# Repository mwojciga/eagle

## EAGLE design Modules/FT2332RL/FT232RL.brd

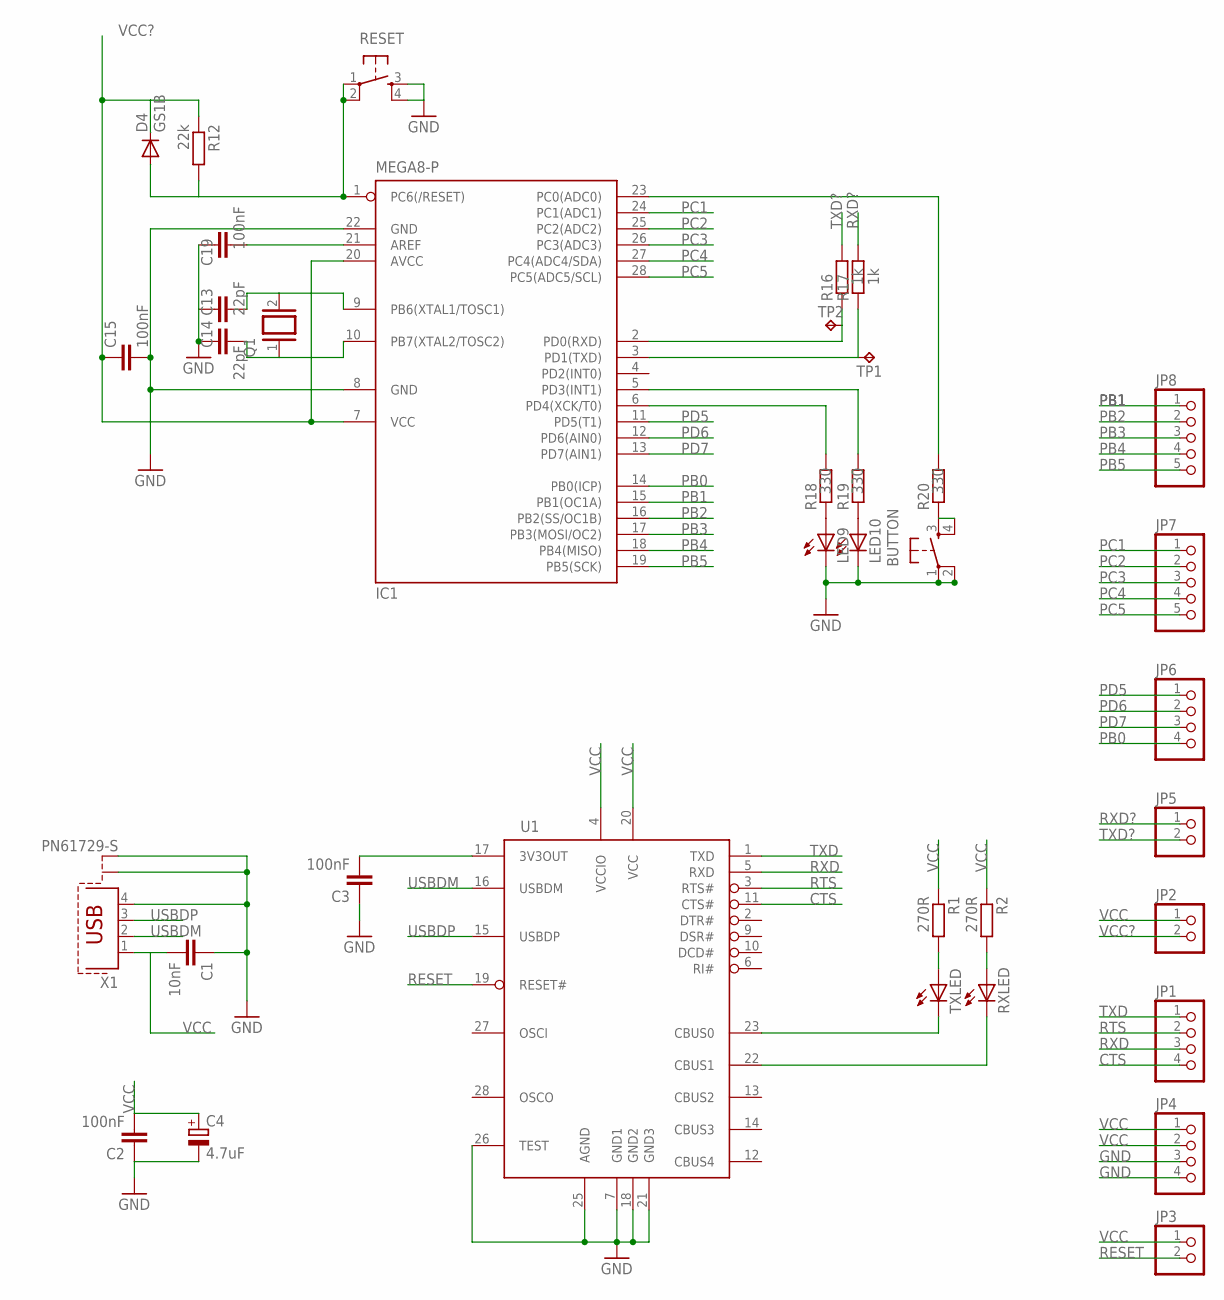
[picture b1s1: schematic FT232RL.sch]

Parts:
BUTTON: TAC_SWITCHSMD; TACTILE_SWITCH_SMD
C1: 10nF; C0805
C2, C3, C15, C19: 100nF; C0805
C4: 4.7uF; E1,8-4
C13, C14: 22pF; C0805
D4: GS1B; DO214AC
IC1: MEGA8-P; DIL28-3
JP1, JP4, JP6: PINHD-1X4; 1X04
JP2, JP3, JP5: PINHD-1X2; 1X02
JP7, JP8: PINHD-1X5; 1X05
LED9, LED10: LEDSMT1206; 1206
Q1: XTAL; Q
R1, R2: 270R; R0805
R12: 22k; R0805
R16, R17: 1k; R0805
R18, R19, R20: 330; R0805
RESET: TAC_SWITCHSMD; TACTILE_SWITCH_SMD
RXLED: LEDSML1206; SML1206
TP1, TP2: TPTP13R; TP13R
TXLED: LEDSML1206; SML1206
U1: FT232RL; SSOP28DB
X1: PN61729-S

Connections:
CTS: JP1.4, U1.11 (CTS#)
GND: BUTTON.1, BUTTON.2, C1.1, C2.1, C3.1, C4.-, C13.1, C14.1, C15.2, C19.2, IC1.8 (GND), IC1.22 (GND), JP4.3, JP4.4, LED9.C, LED10.C, RESET.3, RESET.4, U1.7 (GND1), U1.18 (GND2), U1.21 (GND3), U1.25 (AGND), U1.26 (TEST), X1.4, X1.S1, X1.S2
unnamed: TXLED.C, U1.23 (CBUS0)
unnamed: RXLED.C, U1.22 (CBUS1)
unnamed: R1.2, TXLED.A
unnamed: R2.2, RXLED.A
unnamed: C3.2, U1.17 (3V3OUT)
unnamed: IC1.2 (PD0(RXD)), R16.1, TP2.TP
unnamed: IC1.3 (PD1(TXD)), R17.1, TP1.TP
unnamed: C19.1, IC1.21 (AREF)
unnamed: C14.2, IC1.10 (PB7(XTAL2/TOSC2)), Q1.1
unnamed: C13.2, IC1.9 (PB6(XTAL1/TOSC1)), Q1.2
unnamed: D4.A, IC1.1 (PC6(/RESET)), R12.2, RESET.1, RESET.2
unnamed: BUTTON.3, BUTTON.4, R20.1
unnamed: IC1.6 (PD4(XCK/T0)), R18.2
unnamed: IC1.5 (PD3(INT1)), R19.2
unnamed: IC1.23 (PC0(ADC0)), R20.2
unnamed: LED9.A, R18.1
unnamed: LED10.A, R19.1
PB0: IC1.14 (PB0(ICP)), JP6.4
PB1: IC1.15 (PB1(OC1A)), JP8.1
PB2: IC1.16 (PB2(SS/OC1B)), JP8.2
PB3: IC1.17 (PB3(MOSI/OC2)), JP8.3
PB4: IC1.18 (PB4(MISO)), JP8.4
PB5: IC1.19 (PB5(SCK)), JP8.5
PC1: IC1.24 (PC1(ADC1)), JP7.1
PC2: IC1.25 (PC2(ADC2)), JP7.2
PC3: IC1.26 (PC3(ADC3)), JP7.3
PC4: IC1.27 (PC4(ADC4/SDA)), JP7.4
PC5: IC1.28 (PC5(ADC5/SCL)), JP7.5
PD5: IC1.11 (PD5(T1)), JP6.1
PD6: IC1.12 (PD6(AIN0)), JP6.2
PD7: IC1.13 (PD7(AIN1)), JP6.3
RESET: JP3.2, U1.19 (RESET#)
RTS: JP1.2, U1.3 (RTS#)
RXD: JP1.3, U1.5 (RXD)
RXD?: JP5.1, R17.2
TXD: JP1.1, U1.1 (TXD)
TXD?: JP5.2, R16.2
USBDM: U1.16 (USBDM), X1.2
USBDP: U1.15 (USBDP), X1.3
VCC: C1.2, C2.2, C4.+, JP2.1, JP3.1, JP4.1, JP4.2, R1.1, R2.1, U1.4 (VCCIO), U1.20 (VCC), X1.1
VCC?: C15.1, D4.C, IC1.7 (VCC), IC1.20 (AVCC), JP2.2, R12.1

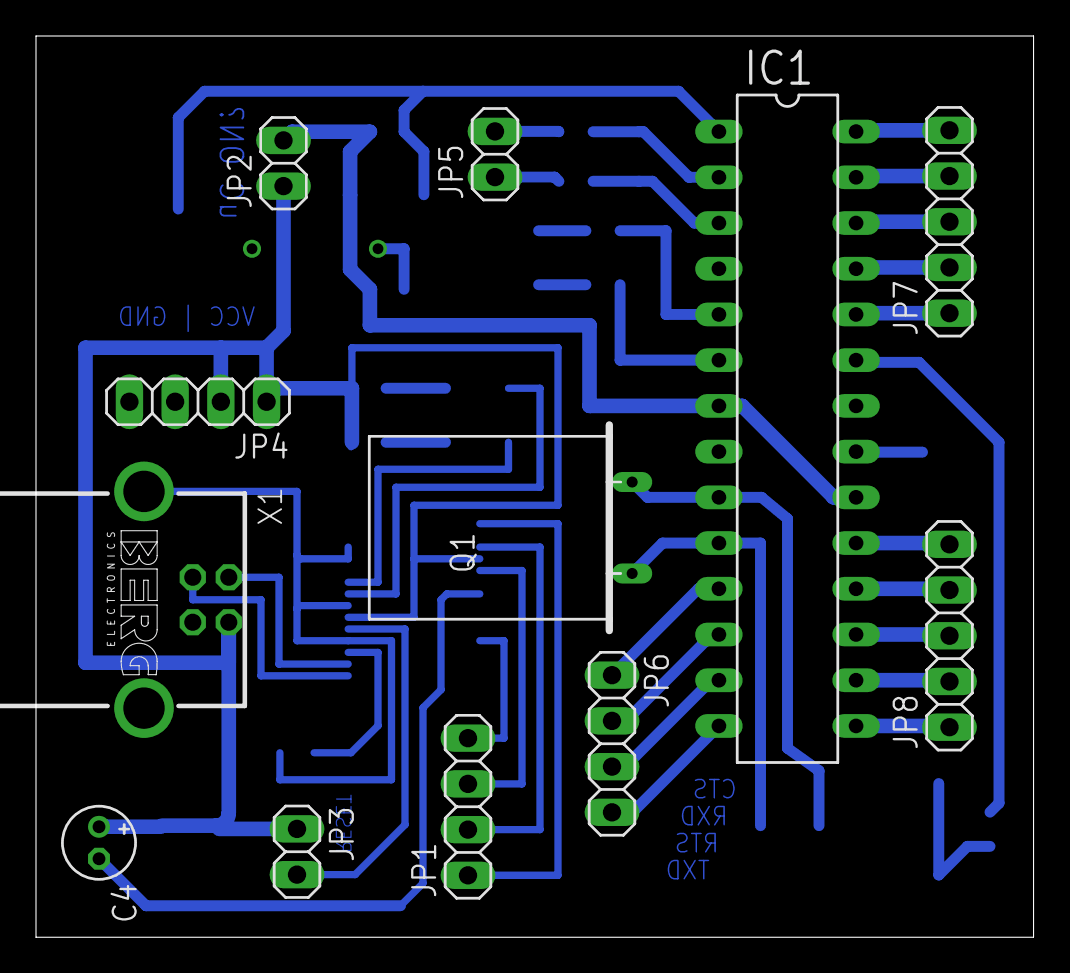
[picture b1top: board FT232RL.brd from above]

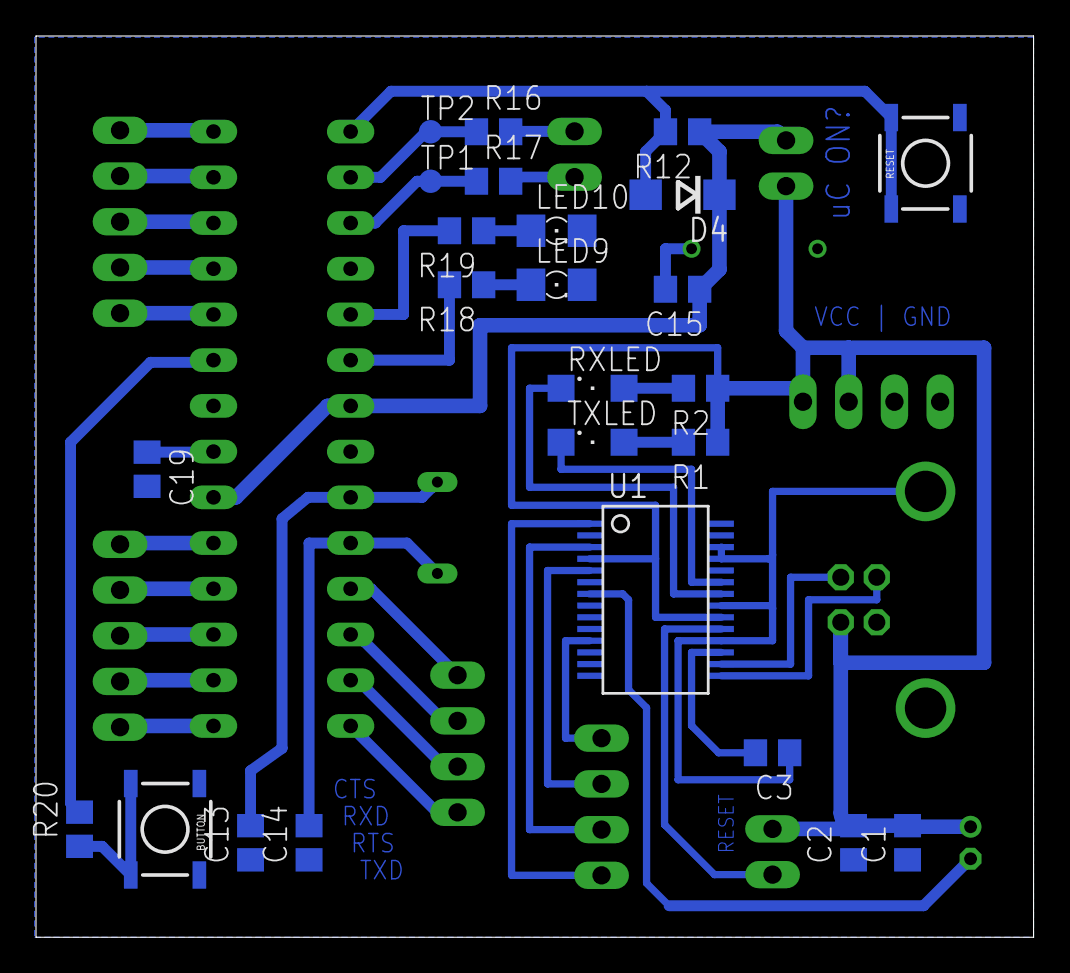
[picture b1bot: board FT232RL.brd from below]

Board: 2 copper layers, 55.4 x 50.1 mm, 37 parts (25 on the bottom side), 43 nets.

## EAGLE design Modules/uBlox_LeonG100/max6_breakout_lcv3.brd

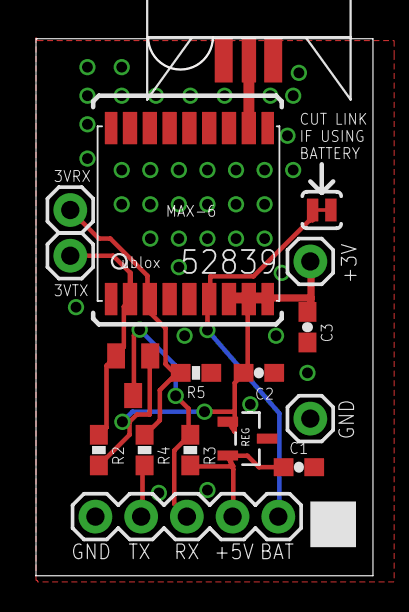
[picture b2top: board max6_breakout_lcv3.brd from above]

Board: 2 copper layers, 18.7 x 29.8 mm, 17 parts (0 on the bottom side), 9 nets.

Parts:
C1, C2, C3: 100nF; 0603-CAP
JP1: 1X05
JP2, JP3, JP4, JP5: M01PTH; 1X01
R2, R3, R4, R5: 10K; 0603-RES
SJ1: SOLDERJUMPERTRACE; SJ_2S-TRACE
U1: LM3480IM3-3.3; SOT95P251X112-3N
U$1: UBLOX_MAX-6
U$2: SARANTEL-SR1202
U$3: BSS138

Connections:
GND: C1.2, C2.2, C3.2, JP1.1, JP2.1, R5.1, SJ1.2, U1.3, U$1.1_GND, U$1.10_GND, U$1.12_GND, U$2.GND1, U$2.GND2
unnamed: U$1.11_RF_IN, U$2.FEED
RX3V3: JP4.1, R4.1, R5.2, U$1.3_RXD1
RX5V: JP1.3, R3.1, U$3.D
TX3V3: JP5.1, R2.1, U$1.2_TXD1, U$3.S
TX5V: JP1.2, R4.2
V5V: C1.1, JP1.4, R3.2, U1.2
VCC: C2.1, C3.1, JP3.1, R2.2, U1.1, U$1.7_VCC_IO, U$1.8_VCC, U$1.9_V_RESET, U$3.G
V_BCKP: JP1.5, SJ1.1, U$1.6_V_BCKP

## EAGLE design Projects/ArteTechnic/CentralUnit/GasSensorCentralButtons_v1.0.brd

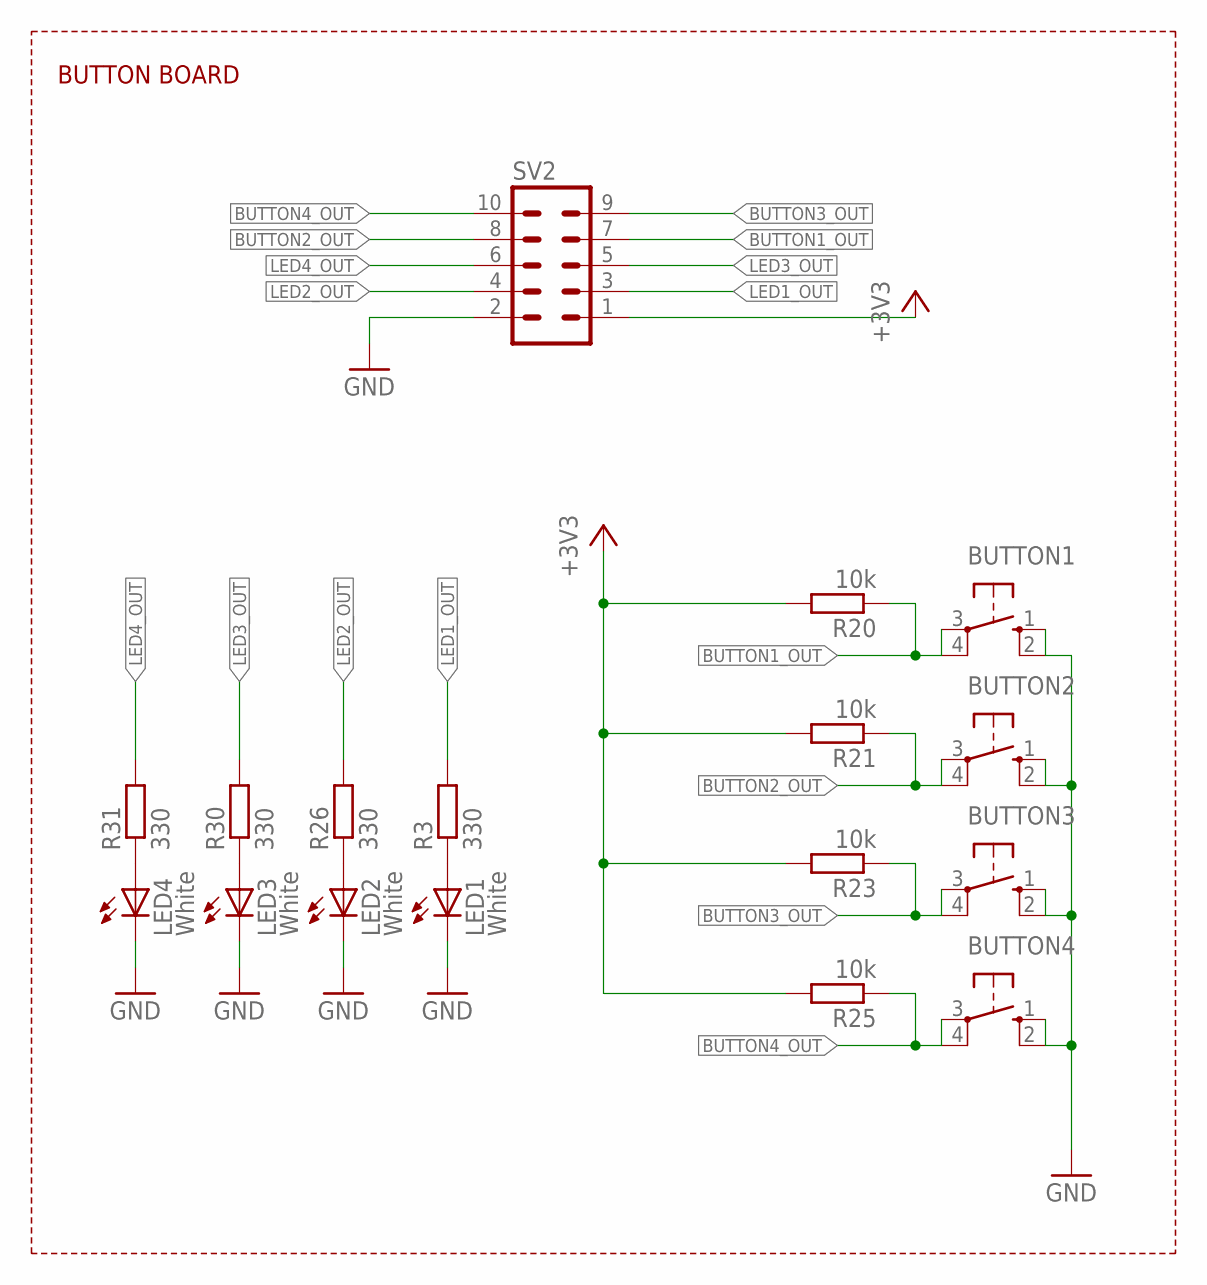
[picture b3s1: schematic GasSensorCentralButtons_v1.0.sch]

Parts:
BUTTON1, BUTTON2, BUTTON3, BUTTON4: 10-XX; B3F-10XX
LED1, LED2, LED3, LED4: White; LED3MM
R3, R26, R30, R31: 330; 0207/10
R20, R21, R23, R25: 10k; 0207/10
SV2: ML10

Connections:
+3V3: R20.2, R21.2, R23.2, R25.2, SV2.1
BUTTON1_OUT: BUTTON1.3, BUTTON1.4 (P1), R20.1, SV2.7
BUTTON2_OUT: BUTTON2.3, BUTTON2.4 (P1), R21.1, SV2.8
BUTTON3_OUT: BUTTON3.3, BUTTON3.4 (P1), R23.1, SV2.9
BUTTON4_OUT: BUTTON4.3, BUTTON4.4 (P1), R25.1, SV2.10
GND: BUTTON1.1 (S), BUTTON1.2 (S1), BUTTON2.1 (S), BUTTON2.2 (S1), BUTTON3.1 (S), BUTTON3.2 (S1), BUTTON4.1 (S), BUTTON4.2 (S1), LED1.K (C), LED2.K (C), LED3.K (C), LED4.K (C), SV2.2
LED1_OUT: R3.2, SV2.3
LED2_OUT: R26.2, SV2.4
LED3_OUT: R30.2, SV2.5
LED4_OUT: R31.2, SV2.6
unnamed: LED1.A, R3.1
unnamed: LED2.A, R26.1
unnamed: LED3.A, R30.1
unnamed: LED4.A, R31.1

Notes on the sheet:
BUTTON BOARD

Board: 2 copper layers, 17 parts (0 on the bottom side), 14 nets, no tracks yet.

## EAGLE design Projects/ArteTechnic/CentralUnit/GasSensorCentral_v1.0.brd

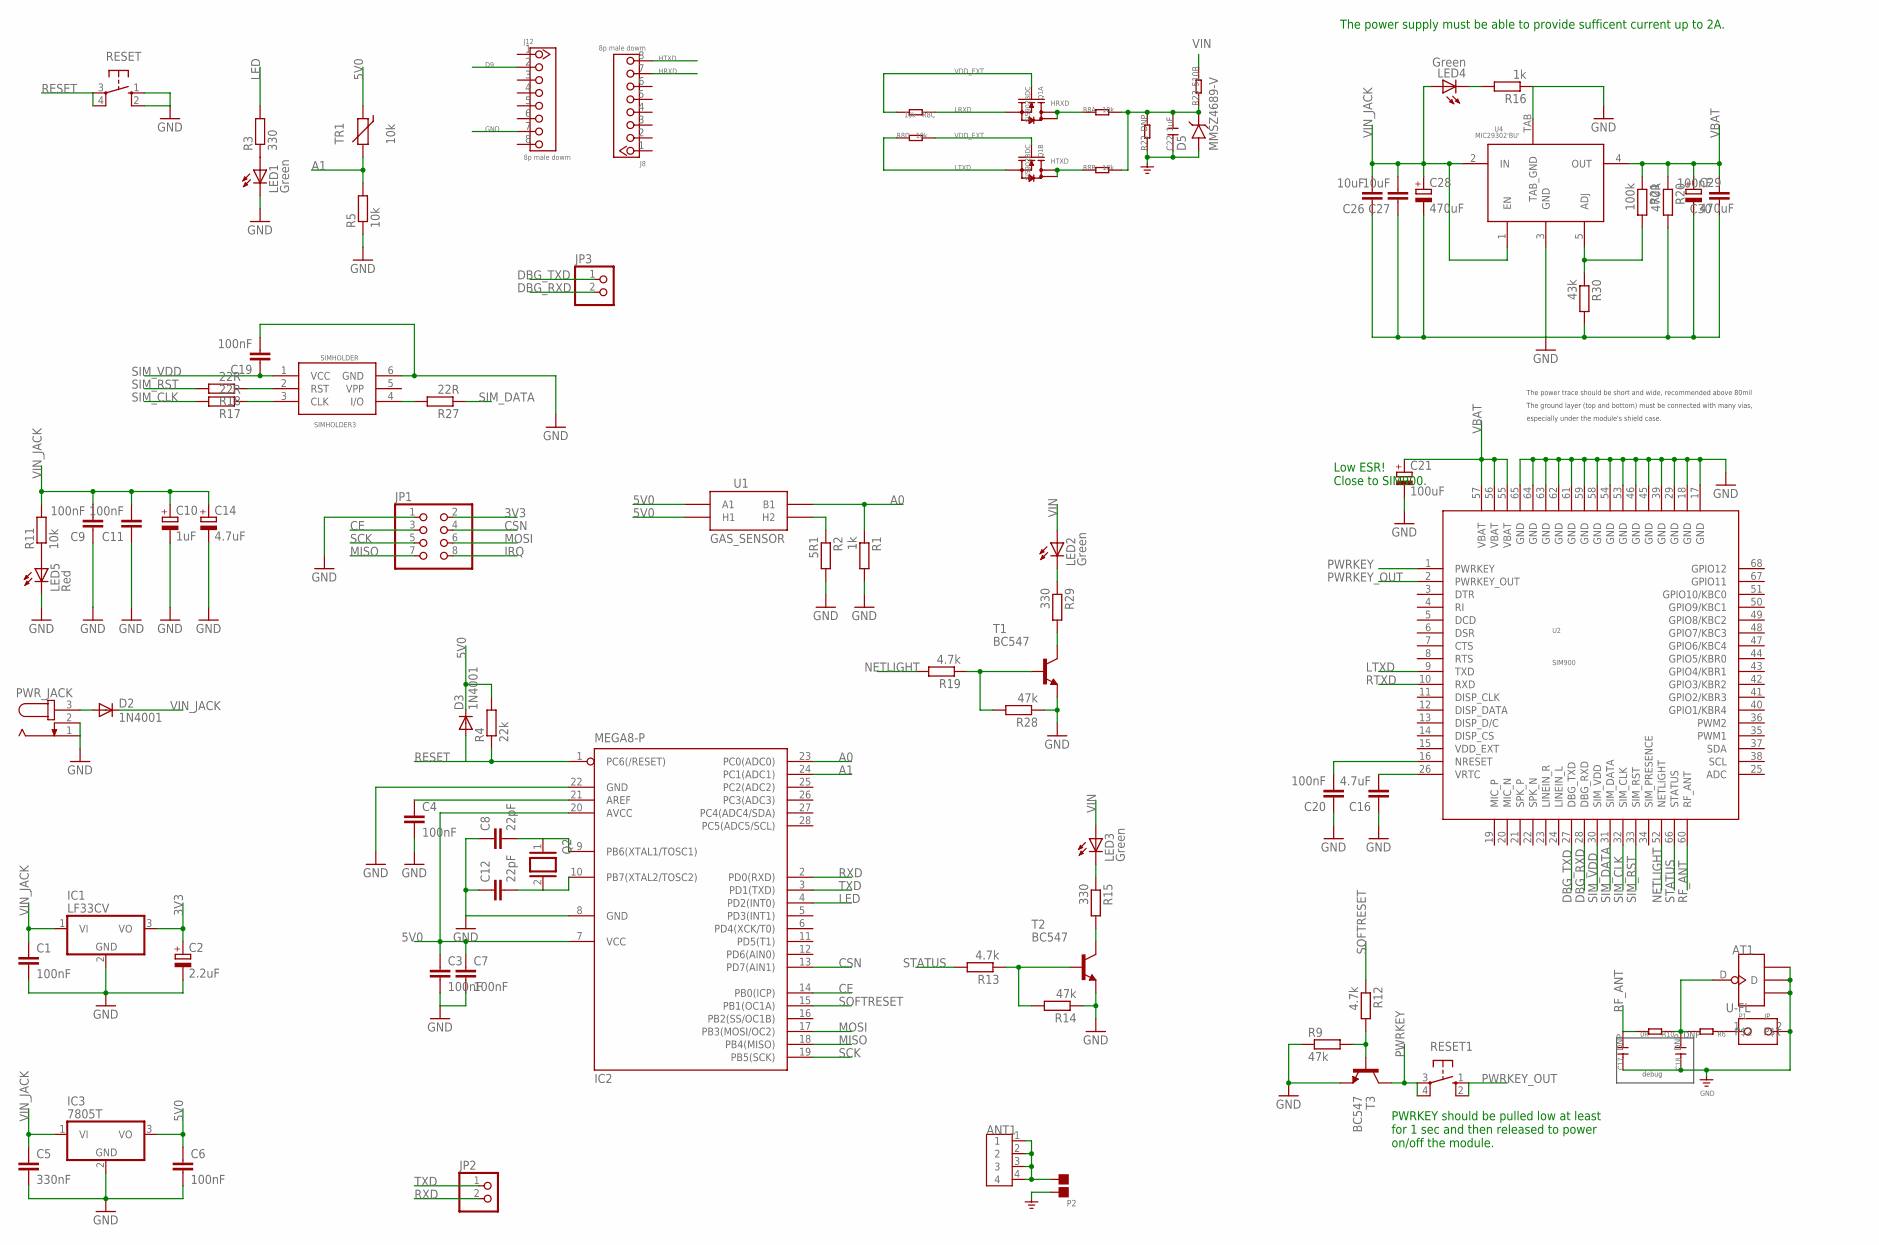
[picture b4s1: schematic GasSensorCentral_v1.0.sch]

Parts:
ANT1: ANTENNA-SMA-IPX; SMA-TO-IPX
AT1: U-FL; 4P-U-FL
C1, C3, C4, C6, C7, C9, C11, C19, C20, C30: 100nF; C025-025X050
C2: 2.2uF; E2,5-5
C5: 330nF; C025-025X050
C8, C12: 22pF; C025-025X050
C10: 1uF; E2,5-5
C14: 4.7uF; E2,5-5
C16: 4.7uF; C025-025X050
C17, C18: DNP; 0402
C21: 100uF; E2,5-5
C22: 1uF; 0603
C26, C27: 10uF; C025-025X050
C28, C29: 470uF; E2,5-5
D2, D3: 1N4001; DO41-10
D5: MMSZ4689-V; SOD123-2.7X1.6
IC1: LF33CV; TO220H
IC2: MEGA8-P; DIL28-3
IC3: 7805T; TO220H
J8, J12: 8p male dowm; CK_1X8
JP1: PINHD-2X4; 2X04
JP2, JP3: PINHD-1X2/90; 1X02/90
LED1, LED2, LED3, LED4: Green; LED3MM
LED5: Red; LED3MM
P1: JP
P2: PAD-JUMPER-2P; 2P-SMD-1.78X1.27
PWR_JACK: JACK-PLUG0; SPC4077
Q1: Si5902BDC; 1206-8
Q2: XTAL/S; QS
R1, R16: 1k; 0207/10
R2: 5R1; 0207/10
R3, R15, R29: 330; 0207/10
R4: 22k; 0207/10
R5, R11: 10k; 0207/10
R6: DNP; 0402
R8: 10k; 1206-8-3.3X2.4
R9, R14, R28: 47k; 0207/10
R10: 0R; 0402
R12, R13, R19: 4.7k; 0207/10
R17, R18, R27: 22R; 0207/10
R20: 470R; 0207/10
R21: 100k; 0207/10
R22: DNP; 0603
R23: 510R; 0603
R30: 43k; 0207/10
RESET, RESET1: 10-XX; B3F-10XX
SIMHOLDER: SIMHOLDER3
T1, T2, T3: BC547; TO92
TR1: 10k; RS-2,5
U1: GAS_SENSOR; MQ-3
U2: SIM900
U4: MIC29302'BU'; TO-263

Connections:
3V3: C2.+, IC1.3 (VO), JP1.2
5V0: C3.1, C6.1, C7.1, D3.C, IC2.7 (VCC), IC2.20 (AVCC), IC3.3 (VO), R4.2, TR1.1, U1.A1, U1.HA (H1)
A0: IC2.23 (PC0(ADC0)), R1.1, U1.B1
A1: IC2.24 (PC1(ADC1)), R5.2, TR1.2
CE: IC2.14 (PB0(ICP)), JP1.3
CSN: IC2.13 (PD7(AIN1)), JP1.4
D9: J12.2
DBG_RXD: JP3.2, U2.28 (DBG_RXD)
DBG_TXD: JP3.1, U2.27 (DBG_TXD)
GND: AT1.GND1, AT1.GND2, AT1.GND3, C1.2, C2.-, C3.2, C4.2, C5.2, C6.2, C7.2, C8.1, C9.1, C10.-, C11.1, C12.1, C14.-, C16.1, C17.1, C18.1, C19.2, C20.1, C21.-, C22.1, C26.1, C27.1, C28.-, C29.-, C30.1, D5.1, IC1.2 (GND), IC2.8 (GND), IC2.22 (GND), IC3.2 (GND), J12.7, JP1.1, LED1.K (C), LED5.K (C), P1.2, P2.2, PWR_JACK.1, PWR_JACK.2, R1.2, R2.2, R5.1, R9.1, R14.1, R16.1, R20.2, R22.1, R28.1, R30.2, RESET.1 (S), RESET.2 (S1), SIMHOLDER.6 (GND), T1.1 (E), T2.1 (E), T3.1 (E), U2.17 (GND), U2.18 (GND), U2.29 (GND), U2.39 (GND), U2.45 (GND), U2.46 (GND), U2.53 (GND), U2.54 (GND), U2.58 (GND), U2.59 (GND), U2.61 (GND), U2.62 (GND), U2.63 (GND), U2.64 (GND), U2.65 (GND), U4.3 (GND), U4.TAB (TAB_GND)
HRXD: J8.7, Q1.7 (D), Q1.8 (D), R8.1
HTXD: J8.8, Q1.5 (D), Q1.6 (D), R8.2 (1)
IRQ: JP1.8
LED: IC2.4 (PD2(INT0)), R3.2
LRXD: Q1.1 (S), R8.3 (1)
LTXD: Q1.3 (S), R8.4 (1), U2.9 (TXD)
MISO: IC2.18 (PB4(MISO)), JP1.7
MOSI: IC2.17 (PB3(MOSI/OC2)), JP1.6
unnamed: C4.1, IC2.21 (AREF)
unnamed: R2.1, U1.HB (H2)
unnamed: D2.A, PWR_JACK.3
unnamed: LED1.A, R3.1
unnamed: R27.2, SIMHOLDER.4 (I/O)
unnamed: LED2.K (C), R29.1
unnamed: R29.2, T1.3 (C)
unnamed: R13.1, R14.2, T2.2 (B)
unnamed: LED5.A, R11.1
unnamed: LED3.K (C), R15.1
unnamed: R15.2, T2.3 (C)
unnamed: C20.2, U2.16 (NRESET)
unnamed: R9.2, R12.2, T3.2 (B)
unnamed: R19.1, R28.2, T1.2 (B)
unnamed: R21.2, R30.1, U4.5 (ADJ)
unnamed: C16.2, U2.26 (VRTC)
unnamed: AT1.D, C18.2, R6.2, R10.1
unnamed: P1.1, R6.1
unnamed: LED4.K (C), R16.2
unnamed: R18.1, SIMHOLDER.2 (RST)
unnamed: R17.1, SIMHOLDER.3 (CLK)
unnamed: C8.2, IC2.9 (PB6(XTAL1/TOSC1)), Q2.1
unnamed: C12.2, IC2.10 (PB7(XTAL2/TOSC2)), Q2.2
unnamed: C22.2, D5.2, R8.7 (2), R8.8 (2), R22.2, R23.1
unnamed: ANT1.1, ANT1.2, ANT1.3, ANT1.4, P2.1
NETLIGHT: R19.2, U2.52 (NETLIGHT)
PWRKEY: RESET1.3, RESET1.4 (P1), T3.3 (C), U2.1 (PWRKEY)
PWRKEY_OUT: RESET1.1 (S), RESET1.2 (S1), U2.2 (PWRKEY_OUT)
RESET: D3.A, IC2.1 (PC6(/RESET)), R4.1, RESET.3, RESET.4 (P1)
RF_ANT: C17.2, R10.2, U2.60 (RF_ANT)
RTXD: U2.10 (RXD)
RXD: IC2.2 (PD0(RXD)), JP2.2
SCK: IC2.19 (PB5(SCK)), JP1.5
SIM_CLK: R17.2, U2.32 (SIM_CLK)
SIM_DATA: R27.1, U2.31 (SIM_DATA)
SIM_RST: R18.2, U2.33 (SIM_RST)
SIM_VDD: C19.1, SIMHOLDER.1 (VCC), U2.30 (SIM_VDD)
SOFTRESET: IC2.15 (PB1(OC1A)), R12.1
STATUS: R13.2, U2.66 (STATUS)
TXD: IC2.3 (PD1(TXD)), JP2.1
VBAT: C21.+, C29.+, C30.2, R20.1, R21.1, U2.55 (VBAT), U2.56 (VBAT), U2.57 (VBAT), U4.4 (OUT)
VDD_EXT: Q1.2 (G), Q1.4 (G), R8.5 (2), R8.6 (2)
VIN: LED2.A, LED3.A, R23.2
VIN_JACK: C1.1, C5.1, C9.2, C10.+, C11.2, C14.+, C26.2, C27.2, C28.+, D2.C, IC1.1 (VI), IC3.1 (VI), LED4.A, R11.2, U4.1 (EN), U4.2 (IN)

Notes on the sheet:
debug
The power trace should be short and wide, recommended above 80mil
The ground layer (top and bottom) must be connected with many vias,
especially under the module's shield case.
PWRKEY should be pulled low at least for 1 sec and then released to power on/off the module.
The power supply must be able to provide sufficent current up to 2A.
Low ESR! Close to SIM900.

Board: 2 copper layers, 84 parts (0 on the bottom side), 59 nets, no tracks yet.

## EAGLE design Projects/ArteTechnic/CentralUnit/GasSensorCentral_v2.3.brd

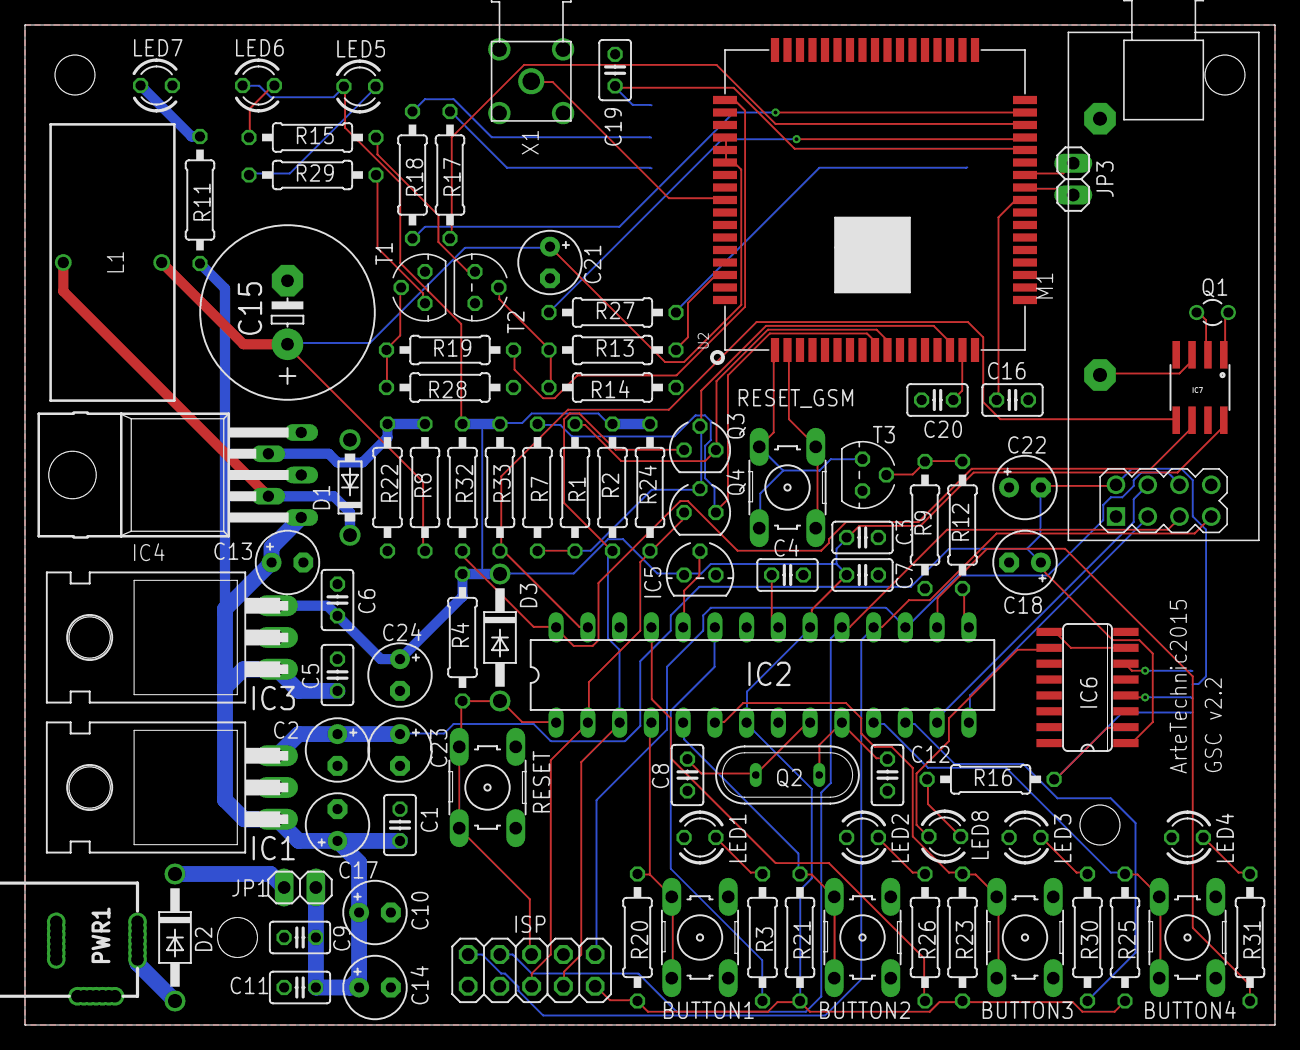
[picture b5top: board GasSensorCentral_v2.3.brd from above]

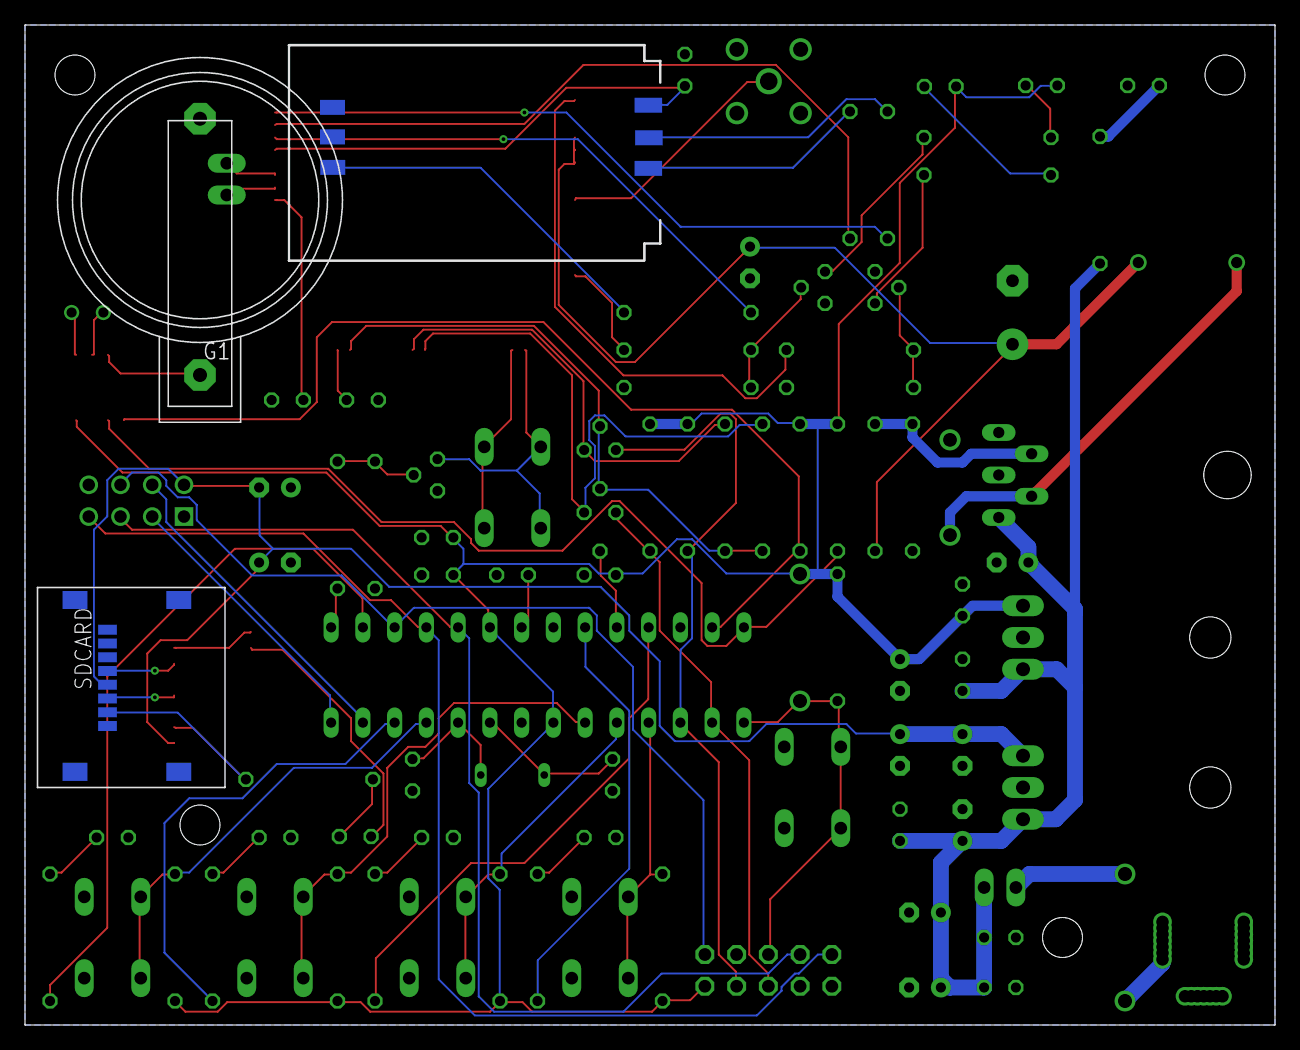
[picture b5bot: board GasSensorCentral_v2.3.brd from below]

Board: 2 copper layers, 100.0 x 80.0 mm, 96 parts (3 on the bottom side), 72 nets.

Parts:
BUTTON1, BUTTON2, BUTTON3, BUTTON4: B3F-10XX
C1, C3, C4, C6, C7, C9, C11, C19, C20: 100nF; C025-025X050
C2: 2.2uF; E2,5-5
C5: 330nF; C025-025X050
C8, C12: 22pF; C025-025X050
C10, C17, C22, C23, C24: 1uF; E2,5-5
C13, C21: 100uF; E2,5-5
C14: 4.7uF; E2,5-5
C15: 3300uF; E5-13
C16: 4.7uF; C025-025X050
C18: 10uF; E2,5-5
D1: 1N5823; DO41-7.6
D2, D3: 1N4001; DO41-10
G1: CR2032H
IC1: LF33CV; TO220H
IC2: MEGA8-P; DIL28-3
IC3: 7805T; TO220H
IC4: LM2576H; TO220-52
IC5: LM35CZ; TO92
IC6: 4050D; SO16
IC7: DS1307SO8; SO08
ISP: 2X05
JP1, JP3: 1X02
L1: 68uH; TJ4-U1
LED1, LED2, LED3, LED4: White; LED3MM
LED5, LED6, LED7: Blue; LED3MM
LED8: Yellow; LED3MM
M1: NRF24L01; WIRELESS-NRD24L01-PA-EXT
PWR1: PWR_JACK_UNI_MILLING
Q1: 32.768K-20PPM; TC26V
Q2: QS
Q3, Q4: BS170; SOT54E
R1, R2, R7, R11, R20, R21, R23, R24, R25, R32, R33: 10k; 0207/10
R3, R15, R26, R29, R30, R31: 330; 0207/10
R4: 22k; 0207/10
R8: 3.6k; 0207/10
R9, R14, R28: 47k; 0207/10
R12, R13, R19: 4.7k; 0207/10
R16: 1k; 0207/10
R17, R18, R27: 22R; 0207/10
R22: 1.5k; 0207/10
RESET: B3F-10XX
RESET_GSM: B3F-10XX
SDCARD: MX-47219-2001
SIMHOLDER: SIMHOLDER3
T1, T2, T3: BC547; TO92
U2: SIM900
X1: BU-SMA-G

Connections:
3V3: C2.+, C18.+, C22.-, C23.+, IC1.3, IC6.1, M1.2, SDCARD.4
5V0: C3.1, C6.1, C7.1, C24.+, D3.C, IC2.7, IC2.20, IC3.3, IC5.1, IC7.8, ISP.2, LED5.A, LED6.A, R2.2, R4.2, R20.2, R21.2, R23.2, R24.2, R25.2, R32.1, R33.1
BUTTON1: BUTTON1.3, BUTTON1.4, IC2.4, R20.1
BUTTON2: BUTTON2.3, BUTTON2.4, IC2.5, R21.1
BUTTON3: BUTTON3.3, BUTTON3.4, IC2.6, R23.1
BUTTON4: BUTTON4.3, BUTTON4.4, IC2.11, R25.1
CE: IC2.14, M1.3
CSN: IC2.13, M1.4
DBG_RXD: JP3.2, U2.28
DBG_TXD: JP3.1, U2.27
GND: BUTTON1.1, BUTTON1.2, BUTTON2.1, BUTTON2.2, BUTTON3.1, BUTTON3.2, BUTTON4.1, BUTTON4.2, C1.2, C2.-, C3.2, C4.2, C5.2, C6.2, C7.2, C8.1, C9.1, C10.-, C11.1, C12.1, C13.-, C14.-, C15.-, C16.1, C17.-, C18.-, C19.2, C20.1, C21.-, C22.+, C23.-, C24.-, D1.A, G1.-, IC1.2, IC2.8, IC2.22, IC3.2, IC4.3, IC4.5, IC5.3, IC6.8, IC6.11, IC6.14, IC7.4, ISP.3, ISP.8, ISP.10, LED1.K, LED2.K, LED3.K, LED4.K, LED7.K, M1.1, PWR1.-, PWR1.--, R9.1, R14.1, R22.2, R28.1, RESET.1, RESET.2, SDCARD.6, SDCARD.G1, SDCARD.G2, SDCARD.G3, SDCARD.G4, SIMHOLDER.6, T1.1, T2.1, T3.1, U2.17, U2.18, U2.29, U2.39, U2.45, U2.46, U2.53, U2.54, U2.58, U2.59, U2.61, U2.62, U2.63, U2.64, U2.65, X1.2, X1.3, X1.4, X1.5
LED1: IC2.23, R3.2
LED2: IC2.25, R26.2
LED3: IC2.12, R30.2
LED4: IC2.16, R31.2
LRXD: Q3.S, R1.1, U2.10
LTXD: Q4.S, R7.1, U2.9
MISO: IC2.18, ISP.9, M1.7
MOSI: IC2.17, ISP.1, M1.6
unnamed: C4.1, IC2.21
unnamed: IC7.2, Q1.1
unnamed: IC4.4, R8.2, R22.1
unnamed: D2.A, PWR1.+
unnamed: LED1.A, R3.1
unnamed: R27.2, SIMHOLDER.4
unnamed: LED5.K, R29.1
unnamed: IC7.1, Q1.2
unnamed: R13.1, R14.2, T2.2
unnamed: LED7.A, R11.1
unnamed: LED6.K, R15.1
unnamed: D1.C, IC4.2, L1.1
unnamed: C20.2, U2.16
unnamed: R9.2, R12.2, T3.2
unnamed: R19.1, R28.2, T1.2
unnamed: G1.+, IC7.3
unnamed: C16.2, U2.26
unnamed: LED2.A, R26.1
unnamed: LED3.A, R30.1
unnamed: LED4.A, R31.1
unnamed: R18.1, SIMHOLDER.2
unnamed: R17.1, SIMHOLDER.3
unnamed: IC6.2, R16.2, SDCARD.2
unnamed: IC6.4, SDCARD.3
unnamed: C8.2, IC2.9, Q2.1
unnamed: IC6.6, SDCARD.5
unnamed: IC6.10, LED8.A
unnamed: LED8.K, R16.1
unnamed: C12.2, IC2.10, Q2.2
NETLIGHT: R19.2, U2.52
NETLIGHT_INFO: R29.2, T1.3
PWRKEY: RESET_GSM.3, RESET_GSM.4, T3.3, U2.1
PWRKEY_OUT: RESET_GSM.1, RESET_GSM.2, U2.2
RESET: D3.A, IC2.1, ISP.5, R4.1, RESET.3, RESET.4
RF_ANT: U2.60, X1.1
RXD: IC2.2, ISP.6, Q4.D, R24.1
SCK: IC2.19, ISP.7, M1.5
SCL: IC2.28, IC7.6, R32.2
SCLK: IC6.7, IC6.9
SDA: IC2.27, IC7.5, R33.2
SIM_CLK: R17.2, U2.32
SIM_DATA: R27.1, U2.31
SIM_RST: R18.2, U2.33
SIM_VDD: C19.1, SIMHOLDER.1, U2.30
SOFTRESET: IC2.15, R12.1
STATUS: R13.2, U2.66
STATUS_INFO: R15.2, T2.3
TEMP: IC2.24, IC5.2
TXD: IC2.3, ISP.4, Q3.D, R2.1
VBAT: C15.+, C21.+, L1.2, R8.1, U2.55, U2.56, U2.57
VDD_EXT: Q3.G, Q4.G, R1.2, R7.2, U2.15
VIN_BUTTON: C1.1, C5.1, C9.2, C10.+, C11.2, C13.+, C14.+, C17.+, IC1.1, IC3.1, IC4.1, JP1.2, R11.2
VIN_JACK: D2.C, JP1.1

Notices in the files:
parts and their libraries:
SparkFun: Licensing: CC v3.0 Share-Alike You are welcome to use this library for commercial purposes.
SparkFun-Sensors: Licensing: Creative Commons ShareAlike 4.0 International - https://creativecommons.org/licenses/by-sa/4.0
